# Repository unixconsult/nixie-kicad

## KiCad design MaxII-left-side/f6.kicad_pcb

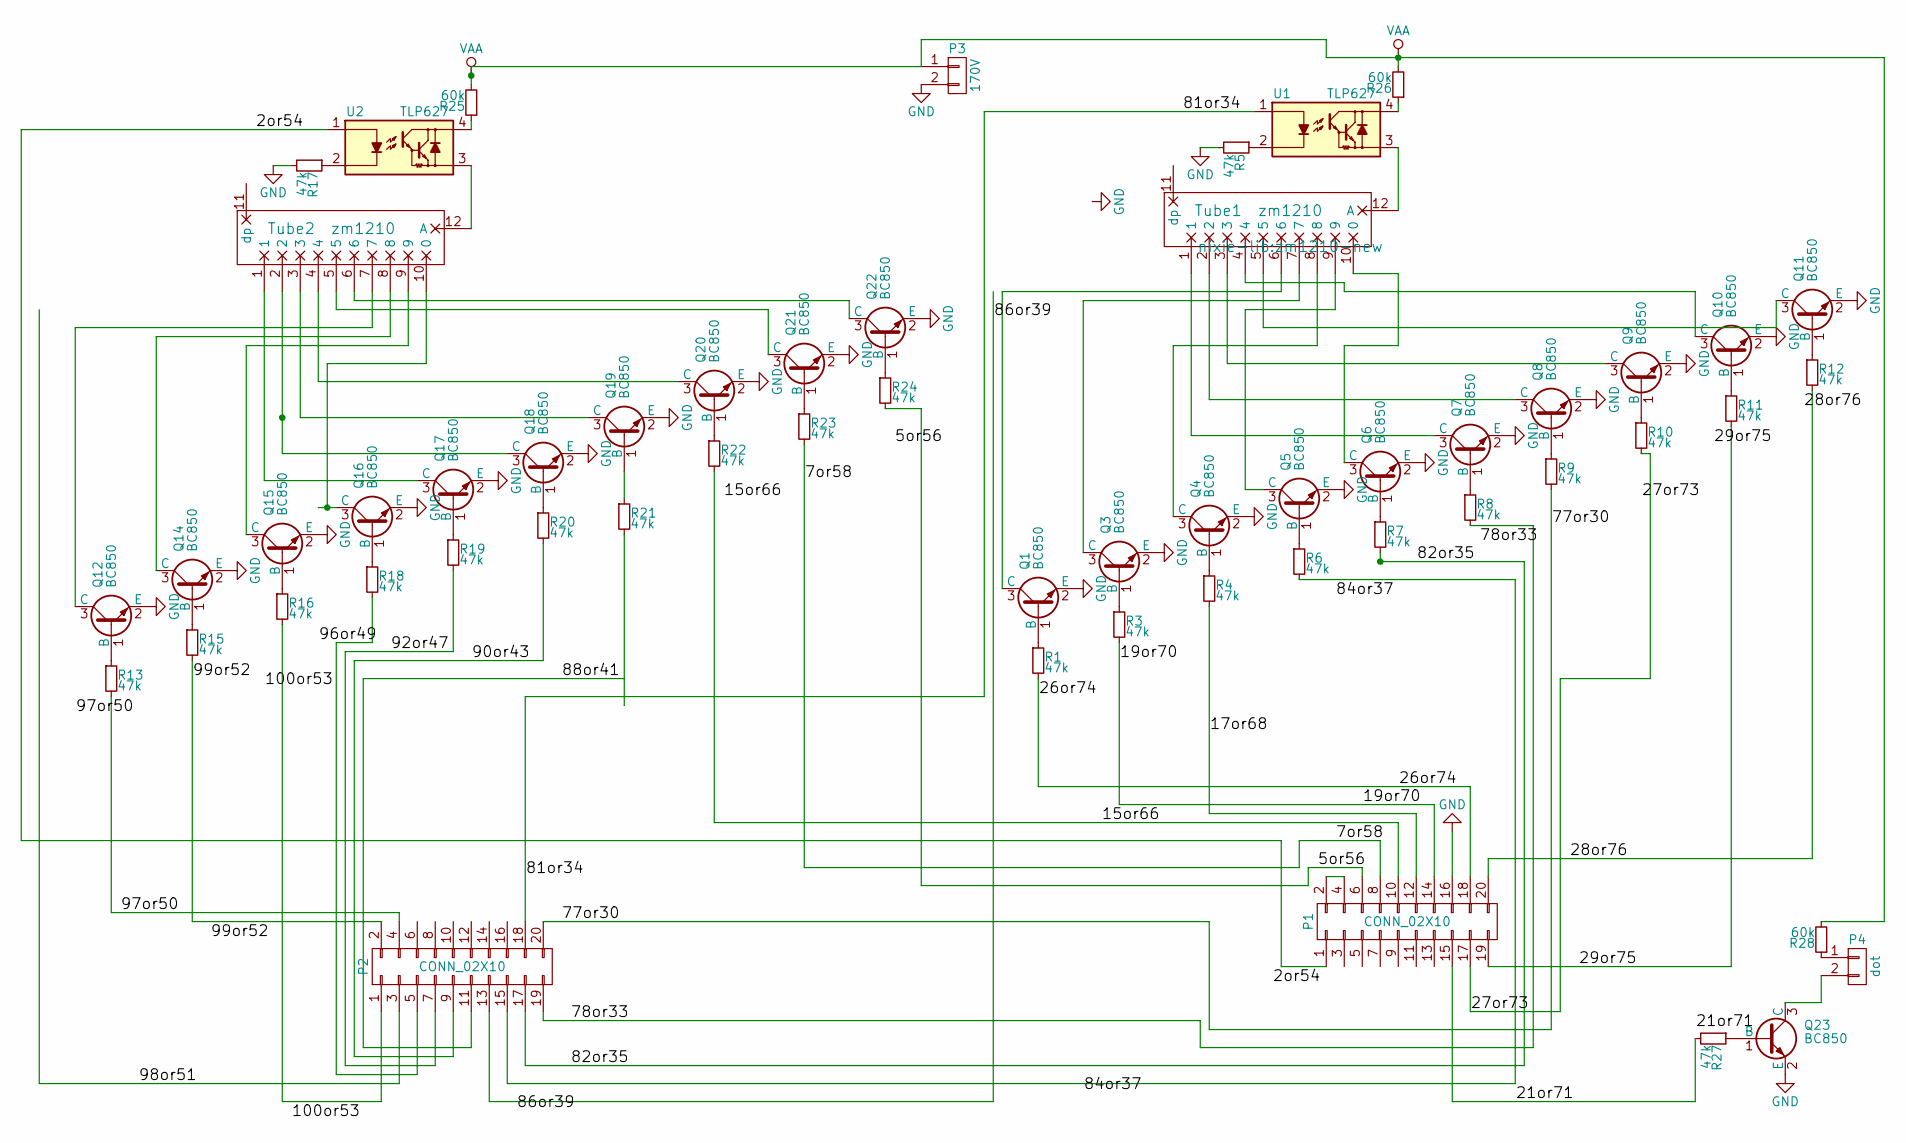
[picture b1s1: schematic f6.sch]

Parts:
P1, P2: CONN_02X10; Pin_Header_Straight_2x10_Pitch2.54mm
P3: 170V; Pin_Header_Straight_1x02_Pitch2.54mm
P4: dot; Pin_Header_Straight_1x02_Pitch2.54mm
Q1, Q3, Q4, Q5, Q6, Q7, Q8, Q9, Q10, Q11, Q12, Q14, Q15, Q16, Q17, Q18, Q19, Q20, Q21, Q22, Q23: BC850; SOT-23
R1, R3, R4, R5, R6, R7, R8, R9, R10, R11, R12, R13, R15, R16, R17, R18, R19, R20, R21, R22, R23, R24, R27: 47k; R_0805
R25, R26, R28: 60k; R_0805
Tube1, Tube2: zm1210; zm1210-new
U1, U2: TLP627; DIP-4_W7.62mm_Socket

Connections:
/2or54: P1.1, U2.1
/5or56: P1.6, R24.2
/7or58: P1.8, R23.2
/15or66: P1.10, R22.2
/17or68: P1.12, R4.2
/19or70: P1.14, R3.2
/21or71: P1.15, R27.2
/26or74: P1.18, R1.2
/27or73: P1.17, R10.2
/28or76: P1.20, R12.2
/29or75: P1.19, R11.2
/77or30: P2.20, R9.2
/78or33: P2.19, R8.2
/81or34: P2.18, U1.1
/82or35: P2.17, R7.2
/86or39: P2.13
/88or41: P2.11
/90or43: P2.9, R20.2
/92or47: P2.7, R19.2
/97or50: P2.4, R13.2
/98or51: P2.3
/99or52: P2.2, R15.2
GND: P1.16, P3.2, Q1.2 (E), Q3.2 (E), Q4.2 (E), Q5.2 (E), Q6.2 (E), Q7.2 (E), Q8.2 (E), Q9.2 (E), Q10.2 (E), Q11.2 (E), Q12.2 (E), Q14.2 (E), Q15.2 (E), Q16.2 (E), Q17.2 (E), Q18.2 (E), Q19.2 (E), Q20.2 (E), Q21.2 (E), Q22.2 (E), Q23.2 (E), R5.2, R17.2
unnamed: P1.2, P1.4
unnamed: P2.1, R16.2
unnamed: P2.5, R18.2
unnamed: P2.15, R6.2
unnamed: P4.1, R28.1
unnamed: P4.2, Q23.3 (C)
unnamed: Q1.1 (B), R1.1
unnamed: Q1.3 (C), Tube1.6
unnamed: Q3.1 (B), R3.1
unnamed: Q3.3 (C), Tube1.7
unnamed: Q4.1 (B), R4.1
unnamed: Q4.3 (C), Tube1.8
unnamed: Q5.1 (B), R6.1
unnamed: Q5.3 (C), Tube1.9
unnamed: Q6.1 (B), R7.1
unnamed: Q6.3 (C), Tube1.10 (0)
unnamed: Q7.1 (B), R8.1
unnamed: Q7.3 (C), Tube1.1
unnamed: Q8.1 (B), R9.1
unnamed: Q8.3 (C), Tube1.2
unnamed: Q9.1 (B), R10.1
unnamed: Q9.3 (C), Tube1.3
unnamed: Q10.1 (B), R11.1
unnamed: Q10.3 (C), Tube1.4
unnamed: Q11.1 (B), R12.1
unnamed: Q11.3 (C), Tube1.5
unnamed: Q12.1 (B), R13.1
unnamed: Q12.3 (C), Tube2.7
unnamed: Q14.1 (B), R15.1
unnamed: Q14.3 (C), Tube2.8
unnamed: Q15.1 (B), R16.1
unnamed: Q15.3 (C), Tube2.9
unnamed: Q16.1 (B), R18.1
unnamed: Q16.3 (C), Tube2.10 (0)
unnamed: Q17.1 (B), R19.1
unnamed: Q17.3 (C), Tube2.1
unnamed: Q18.1 (B), R20.1
unnamed: Q18.3 (C), Tube2.2
unnamed: Q19.1 (B), R21.1
unnamed: Q19.3 (C), Tube2.3
unnamed: Q20.1 (B), R22.1
unnamed: Q20.3 (C), Tube2.4
unnamed: Q21.1 (B), R23.1
unnamed: Q21.3 (C), Tube2.5
unnamed: Q22.1 (B), R24.1
unnamed: Q22.3 (C), Tube2.6
unnamed: Q23.1 (B), R27.1
unnamed: R5.1, U1.2
unnamed: R17.1, U2.2
unnamed: R25.1, U2.4
unnamed: R26.1, U1.4
unnamed: Tube1.12 (A), U1.3
unnamed: Tube2.12 (A), U2.3
VAA: P3.1, R25.2, R26.2, R28.2

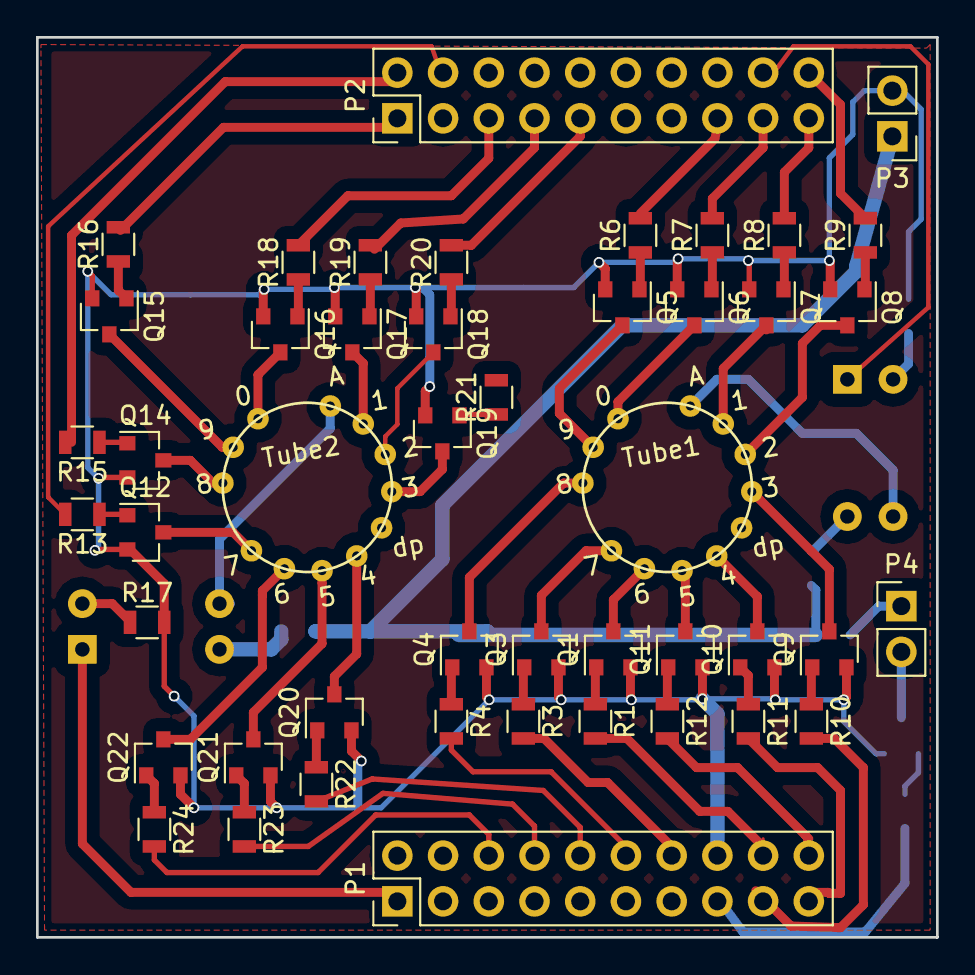
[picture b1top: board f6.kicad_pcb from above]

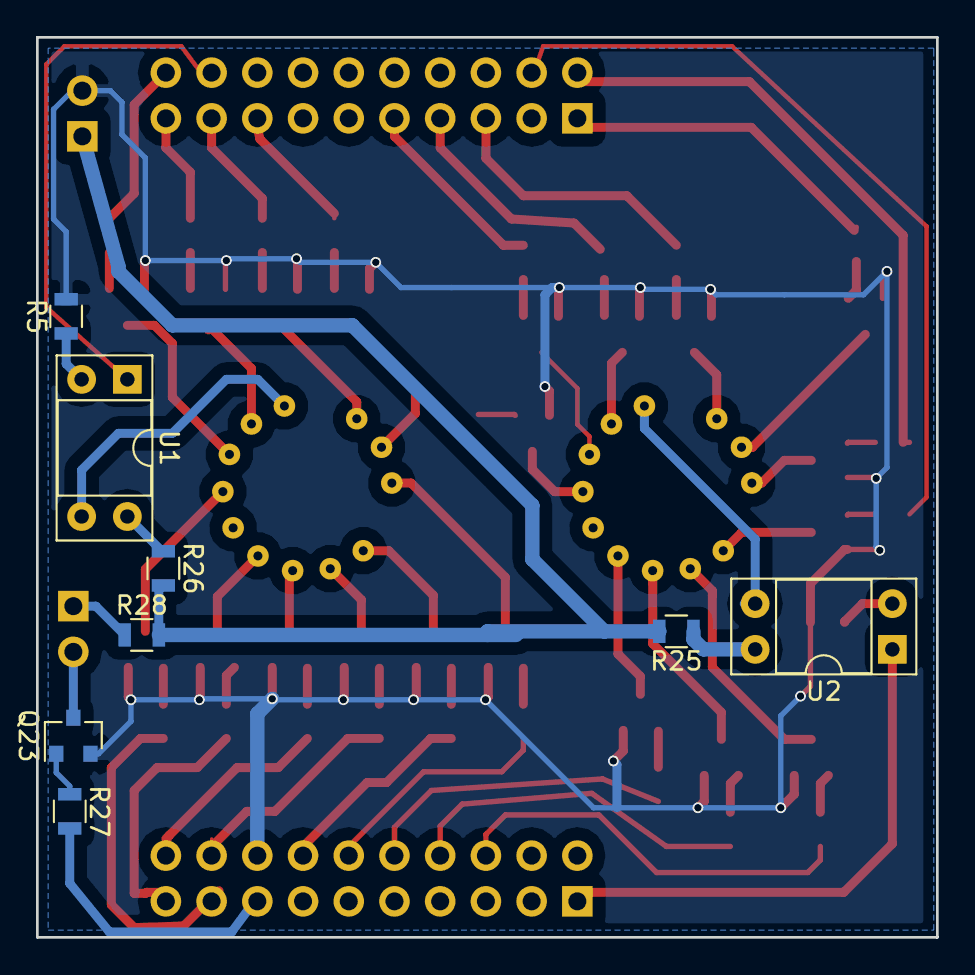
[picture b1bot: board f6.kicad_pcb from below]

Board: 2 copper layers, 50.0 x 50.0 mm, 55 parts (8 on the bottom side), 74 nets.

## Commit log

2018-03-14 3x clk input
2018-03-26 added overview
